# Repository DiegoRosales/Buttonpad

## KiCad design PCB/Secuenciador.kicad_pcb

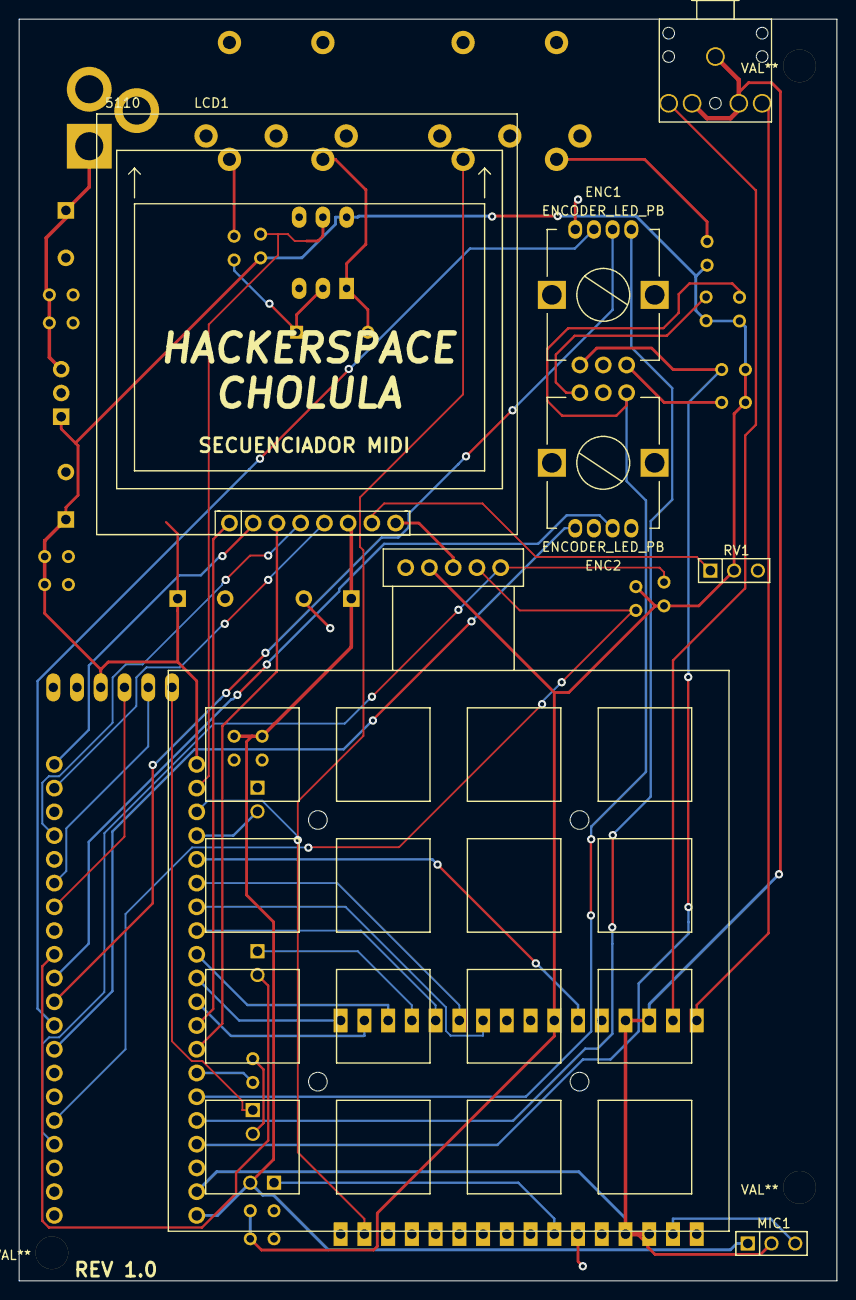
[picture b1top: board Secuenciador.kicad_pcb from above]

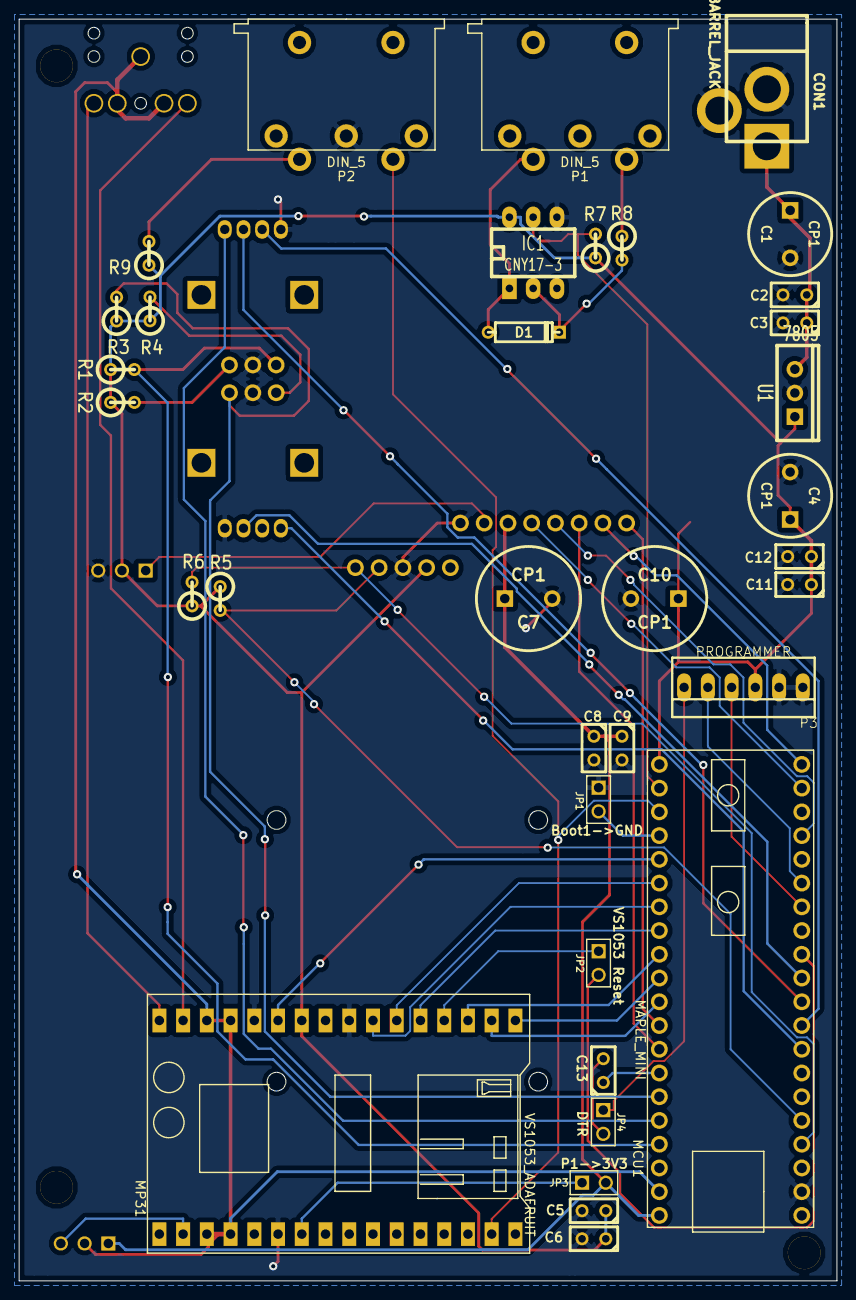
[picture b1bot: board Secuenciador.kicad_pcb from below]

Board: 2 copper layers, 87.5 x 135.0 mm, 45 parts (35 on the bottom side), 47 nets.

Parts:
3.5mm_Screw, 3.5mm_Screw#2, 3.5mm_Screw#3: VAL**; 3.5mm_Screw
BTNPAD1: ADAFRUIT_TRELLIS; Adafruit_trellis
C1, C4: CP1; C2V8
C2, C3, C5, C6, C8, C9, C11, C12, C13: C; C1
C7, C10: CP1; C2V10
CON1: BARREL_JACK; JACK_ALIM
D1: DIODE; D3
ENC1, ENC2: ENCODER_LED_PB; SPARKFUN_ROTARY_ENCODER
IC1: CNY17-3; DIP-6__300_ELL
J1: JACK_ST_2SW_PROPER; Jack_3.5mm_Stereo
JP1, JP2, JP3, JP4: JUMPER; PIN_ARRAY_2X1
LCD1: 5110; Nokia5110_LCD_2
MCU1: MAPLE_MINI; Leaf_maple_mini
MIC1: MIC; PIN_ARRAY_3X1
MP31: VS1053_ADAFRUIT; VS1030_Adafruit
P1, P2: DIN_5; MIDI_CONN
P3: PROGRAMMER; PINHEAD1-6
R1, R2, R3, R4, R5, R6: 10k; R1
R7, R8, R9: R; R1
RV1: POT; PIN_ARRAY_3X1
U1: 7805; TO220_VERT

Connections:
+3.3V: C7.1, C8.1, C9.1, JP3.2, LCD1.6, MCU1.1, MIC1.1
+5V: BTNPAD1.4, C4.1, C5.1, C6.1, C10.1, C11.1, C12.1, IC1.6, MCU1.20, MP31.26, P3.3, R1.1, R2.1, R3.1, R4.1, R5.1, R6.1, R7.1, R9.1, RV1.2, U1.VO
/Boot1: JP1.2, MCU1.17
/CS_3V3: LCD1.2, MCU1.21
/DC_3V3: LCD1.3, MCU1.8
/DISP_LED: LCD1.7, RV1.1
/ENC1_A: ENC1.5, MCU1.4, R1.2
/ENC1_B: ENC1.7, R2.2
/ENC1_L1: ENC1.2, MCU1.32
/ENC1_L2: ENC1.3, MCU1.31
/ENC1_SW: ENC1.4, MCU1.5
/ENC2_A: ENC2.5, MCU1.6, R3.2
/ENC2_B: ENC2.7, R4.2
/ENC2_L1: ENC2.2, MCU1.30
/ENC2_SW: ENC2.4, MCU1.33
/LOUT: J1.T, MP31.31
/MIC+: MIC1.3, MP31.2
/MIDI_IN: IC1.5, MCU1.19, R7.2
/MIDI_OUT: MCU1.18, MP31.15, P2.4
/MOSI_3V3: LCD1.4, MCU1.24
/PROG_DTR: JP4.1, P3.6
/PROG_RX: MCU1.27, P3.4
/PROG_TX: MCU1.26, P3.5
/ROUT: J1.R, MP31.32
/RST_3V3: LCD1.1, MCU1.9
/SCL: BTNPAD1.2, MCU1.36, R5.2
/SCLK_3V3: LCD1.5, MCU1.22
/SDA: BTNPAD1.1, MCU1.37, R6.2
/VS1053_CS: MCU1.12, MP31.19
/VS1053_DREQ: MCU1.16, MP31.27
/VS1053_MISO: MCU1.14, MP31.23
/VS1053_MOSI: MCU1.15, MP31.22
/VS1053_RST: JP2.1, MP31.20
/VS1053_SCLK: MCU1.13, MP31.21
/VS1053_SDCS: MCU1.10, MP31.18
/VS1053_XDCS: MCU1.11, MP31.17
AGND: J1.R_SW, J1.S, J1.T_SW, MCU1.2, MIC1.2, MP31.3, MP31.4, MP31.29, MP31.30
GND: BTNPAD1.3, C1.2, C2.2, C3.2, C4.2, C5.2, C6.2, C7.2, C8.2, C9.2, C10.2, C11.2, C12.2, CON1.2, CON1.3, ENC1.1, ENC1.6, ENC2.1, ENC2.6, IC1.4, JP1.1, LCD1.8, MCU1.39, MP31.6, MP31.24, MP31.28, P2.3, P3.1, P3.2, RV1.3, U1.GND
unnamed: JP2.2, MCU1.29
unnamed: P2.2, R9.2
unnamed: JP3.1, MP31.7
unnamed: D1.1, IC1.1, P1.2
unnamed: D1.2, IC1.2, R8.2
unnamed: P1.4, R8.1
unnamed: C13.1, MCU1.7
unnamed: C13.2, JP4.2
VCC: C1.1, C2.1, C3.1, CON1.1, U1.VI

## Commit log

2015-05-15 :neckbeard: Added .gitattributes & .gitignore files
2015-05-15 Buttonpad
2015-05-27 Rev 1.0
